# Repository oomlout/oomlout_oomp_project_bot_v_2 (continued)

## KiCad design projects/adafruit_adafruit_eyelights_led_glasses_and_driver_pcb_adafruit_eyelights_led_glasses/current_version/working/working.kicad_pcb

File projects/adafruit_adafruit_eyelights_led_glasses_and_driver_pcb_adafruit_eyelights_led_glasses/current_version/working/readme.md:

# adafruit_eyelights_led_glasses_and_driver_pcb
 
## summary 
* id: adafruit_adafruit_eyelights_led_glasses_and_driver_pcb_adafruit_eyelights_led_glasses
* user: adafruit
* name: adafruit_eyelights_led_glasses_and_driver_pcb
* board: adafruit_eyelights_led_glasses
* repo: https://github.com/adafruit/Adafruit-EyeLights-LED-Glasses-and-Driver-PCB

* src_file_repo_sch: 
* src_file_repo_sch_link: https://github.com/adafruit/Adafruit-EyeLights-LED-Glasses-and-Driver-PCB/tree/main/
* full details link: https://github.com/oomlout/oomlout_oomp_project_bot_v_2/tree/main/projects/adafruit_adafruit_eyelights_led_glasses_and_driver_pcb_adafruit_eyelights_led_glasses/current_version/working  

## schematic  
  
[schematic (pdf)](working_schematic.pdf) 

## pcb  

[board (pdf)](working.pdf)  

## working_bom
| Id | Designator | Footprint | Quantity | Designation | Supplier and ref |  | None | 
| --- | --- | --- | --- | --- | --- | --- | --- | 
| 1 | C10,C3,C4 | 0603-NO | 3 | 0.1uF |  |  | [''] | 
| 2 | R10,R11 | 0603-NO | 2 | 22 |  |  | [''] | 
| 3 | C7,C9,C6,C8,C5,C1 | 0805-NO | 6 | 10uF |  |  | [''] | 
| 4 | IC1 | SPK0415HM4H | 1 | MIC_PDM_SPK0415 |  |  | [''] | 
| 5 | SW1 | SPST_TACTILE_RA | 1 | TACT_RA |  |  | [''] | 
| 6 | FID2,FID1 | FIDUCIAL_1MM | 2 | FIDUCIAL_1MM |  |  | [''] | 
| 7 | D3 | CHIPLED_0805_NOOUTLINE | 1 | ORANGE |  |  | [''] | 
| 8 | U$16,U$14,U$10,U$12 | SLOT_4MM_PLATED | 4 | MOUNTINGHOLE_SLOT4MM |  |  | [''] | 
| 9 | SW2 | EG1390 | 1 | EG11 |  |  | [''] | 
| 10 | IC2 | SOIC8_150MIL | 1 | GD25Q16 |  |  | [''] | 
| 11 | R7,R1,R8,R6 | 0603-NO | 4 | 100K |  |  | [''] | 
| 12 | SW3 | BTN_KMR2_4.6X2.8 | 1 | KMR2 |  |  | [''] | 
| 13 | R2,R3 | 0603-NO | 2 | 1K |  |  | [''] | 
| 14 | X2 | USB_C_CUSB31-CFM2AX-01-X | 1 | USBC |  |  | [''] | 
| 15 | U3 | SOT23-5 | 1 | MCP73831T-2ACI/OT |  |  | [''] | 
| 16 | LED1 | SK6805_1515 | 1 | WS2812B_SK6805_1515 |  |  | [''] | 
| 17 | R12,R9,R4 | 0603-NO | 3 | 5.1K |  |  | [''] | 
| 18 | D2 | CHIPLED_0805_NOOUTLINE | 1 | RED |  |  | [''] | 
| 19 | JP1 | 1X03_ROUND | 1 |  |  |  | [''] | 
| 20 | CONN1 | JST_SH4 | 1 | STEMMA_I2C_QT |  |  | [''] | 
| 21 | IC4 | LGA16_3X3MM | 1 | LIS3DH |  |  | [''] | 
| 22 | Q3 | SOT23-R | 1 | DMG2305 |  |  | [''] | 
| 23 | Q2 | SOT363 | 1 | BSS138 |  |  | [''] | 
| 24 | R5 | RESPACK_4X0603 | 1 | 10K |  |  | [''] | 
| 25 | U2 | SOT23-5 | 1 | AP2112(3.3V) |  |  | [''] | 
| 26 | MDBT1 | MDBT50 | 1 | MDBT50 |  |  | [''] | 
| 27 | X3 | JSTPH2_BATT | 1 | JSTPH |  |  | [''] | 
| 28 | D1 | SOD-123 | 1 | MBR120 |  |  | [''] | 
| 29 | SJ1 | SOLDERJUMPER_ARROW_NOPASTE | 1 |  |  |  | [''] | 
| 30 | U$63 | PCBFEAT-REV-040 | 1 |  |  |  | [''] | 
| 31 | U$37 | ADAFRUIT_TEXT_20MM | 1 |  |  |  | [''] | 
| 32 | U$28 | STEMMAQT | 1 |  |  |  | [''] | 

## bom_schematic
| Ref | Qnty | Value | Cmp name | Footprint | Description | Vendor | DNP | 
| --- | --- | --- | --- | --- | --- | --- | --- | 
| C1, C5, C6, C7, C8, C9 | 6 | 10uF | CAP_CERAMIC0805-NOOUTLINE | working:0805-NO |  |  |  | 
| C3, C4, C10 | 3 | 0.1uF | CAP_CERAMIC0603_NO | working:0603-NO |  |  |  | 
| CONN1 | 1 | STEMMA_I2C_QT | STEMMA_I2C_QT | working:JST_SH4 |  |  |  | 
| D1 | 1 | MBR120 | DIODE-SCHOTTKYSOD-123 | working:SOD-123 |  |  |  | 
| D2 | 1 | RED | LED0805_NOOUTLINE | working:CHIPLED_0805_NOOUTLINE |  |  |  | 
| D3 | 1 | ORANGE | LED0805_NOOUTLINE | working:CHIPLED_0805_NOOUTLINE |  |  |  | 
| FID1, FID2 | 2 | FIDUCIAL_1MM | FIDUCIAL_1MM | working:FIDUCIAL_1MM |  |  |  | 
| IC1 | 1 | MIC_PDM_SPK0415 | MIC_PDM_SPK0415 | working:SPK0415HM4H |  |  |  | 
| IC2 | 1 | GD25Q16 | SPIFLASH_8PIN | working:SOIC8_150MIL |  |  |  | 
| IC4 | 1 | LIS3DH | ACCEL_LIS3DHTR | working:LGA16_3X3MM |  |  |  | 
| JP1 | 1 | HEADER-1X3ROUND | HEADER-1X3ROUND | working:1X03_ROUND |  |  |  | 
| LED1 | 1 | WS2812B_SK6805_1515 | WS2812B_SK6805_1515 | working:SK6805_1515 |  |  |  | 
| MDBT1 | 1 | MDBT50 | MDBT50 | working:MDBT50 |  |  |  | 
| Q2 | 1 | BSS138 | MOSFET-N_DUAL | working:SOT363 |  |  |  | 
| Q3 | 1 | DMG2305 | MOSFET-P | working:SOT23-R |  |  |  | 
| R1, R6, R7, R8 | 4 | 100K | RESISTOR_0603_NOOUT | working:0603-NO |  |  |  | 
| R2, R3 | 2 | 1K | RESISTOR_0603_NOOUT | working:0603-NO |  |  |  | 
| R4, R9, R12 | 3 | 5.1K | RESISTOR_0603_NOOUT | working:0603-NO |  |  |  | 
| R5 | 1 | 10K | RESISTOR_4PACK | working:RESPACK_4X0603 |  |  |  | 
| R10, R11 | 2 | 22 | RESISTOR_0603_NOOUT | working:0603-NO |  |  |  | 
| SJ1 | 1 | SOLDERJUMPER | SOLDERJUMPER | working:SOLDERJUMPER_ARROW_NOPASTE |  |  |  | 
| SW1 | 1 | TACT_RA | SWITCH_SPST_TACT_RA | working:SPST_TACTILE_RA |  |  |  | 
| SW2 | 1 | EG11 | SWITCH_DPDTEG1390 | working:EG1390 |  |  |  | 
| SW3 | 1 | KMR2 | SWITCH_TACT_SMT4.6X2.8 | working:BTN_KMR2_4.6X2.8 |  |  |  | 
| U2 | 1 | AP2112(3.3V) | VREG_SOT23-5 | working:SOT23-5 |  |  |  | 
| U3 | 1 | MCP73831T-2ACI/OT | MCP73831/2 | working:SOT23-5 |  |  |  | 
| U$10, U$12, U$14, U$16 | 4 | MOUNTINGHOLE_SLOT4MM | MOUNTINGHOLE_SLOT4MM | working:SLOT_4MM_PLATED |  |  |  | 
| X2 | 1 | USBC | USB_C | working:USB_C_CUSB31-CFM2AX-01-X |  |  |  | 
| X3 | 1 | JSTPH | CON_JST_PH_2PIN_BATT | working:JSTPH2_BATT |  |  |  |

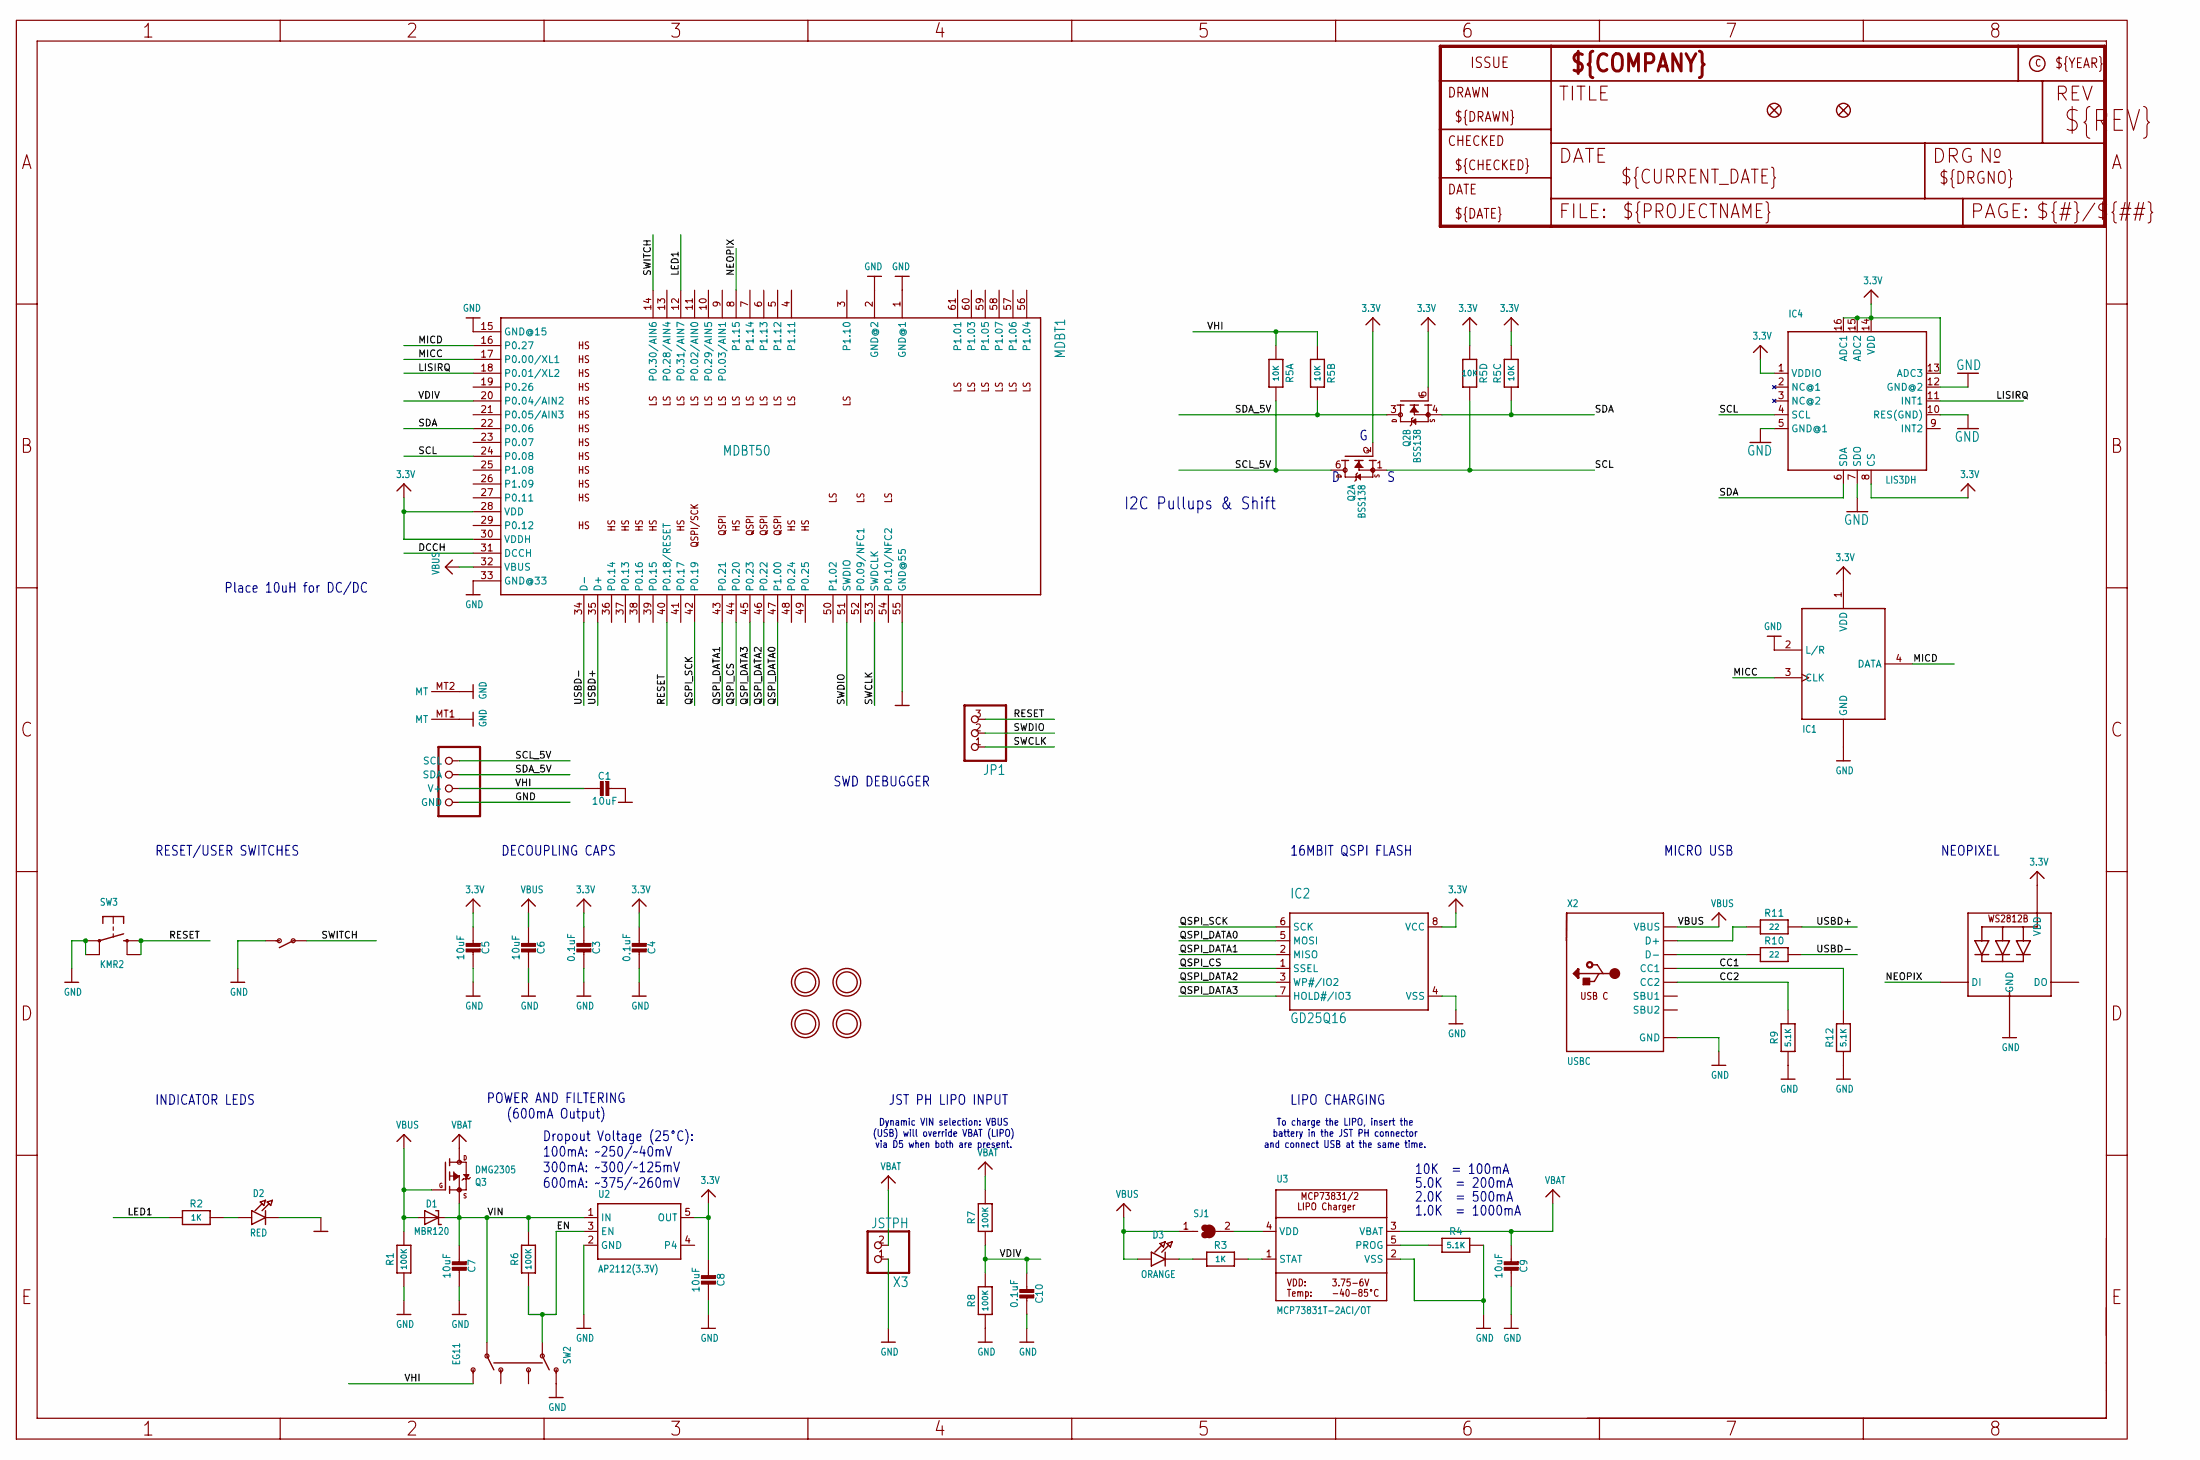
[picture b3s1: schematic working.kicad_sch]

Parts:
C1, C5, C6, C7, C8, C9: 10uF; 0805-NO
C3, C4, C10: 0.1uF; 0603-NO
CONN1: STEMMA_I2C_QT; JST_SH4
D1: MBR120; SOD-123
D2: RED; CHIPLED_0805_NOOUTLINE
D3: ORANGE; CHIPLED_0805_NOOUTLINE
FID1, FID2: FIDUCIAL_1MM
IC1: MIC_PDM_SPK0415; SPK0415HM4H
IC2: GD25Q16; SOIC8_150MIL
IC4: LIS3DH; LGA16_3X3MM
JP1: HEADER-1X3ROUND; 1X03_ROUND
LED1: WS2812B_SK6805_1515; SK6805_1515
MDBT1: MDBT50
Q2: BSS138; SOT363
Q3: DMG2305; SOT23-R
R1, R6, R7, R8: 100K; 0603-NO
R2, R3: 1K; 0603-NO
R4, R9, R12: 5.1K; 0603-NO
R5: 10K; RESPACK_4X0603
R10, R11: 22; 0603-NO
SJ1: SOLDERJUMPER; SOLDERJUMPER_ARROW_NOPASTE
SW1: TACT_RA; SPST_TACTILE_RA
SW2: EG11; EG1390
SW3: KMR2; BTN_KMR2_4.6X2.8
U2: AP2112(3.3V); SOT23-5
U3: MCP73831T-2ACI/OT; SOT23-5
U$10, U$12, U$14, U$16: MOUNTINGHOLE_SLOT4MM; SLOT_4MM_PLATED
X2: USBC; USB_C_CUSB31-CFM2AX-01-X
X3: JSTPH; JSTPH2_BATT

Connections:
3.3V: C3.2, C4.2, C5.2, C8.2, IC1.1 (VDD), IC2.8 (VCC), IC4.1 (VDDIO), IC4.8 (CS), IC4.13 (ADC3), IC4.14 (VDD), IC4.15 (ADC2), IC4.16 (ADC1), LED1.2 (VDD), MDBT1.28 (VDD), MDBT1.30 (VDDH), Q2.2 (G), Q2.5 (G), R5.3 (1), R5.5 (2), U2.5 (OUT)
CC1: R12.2, X2.A5 (CC1)
CC2: R9.2, X2.B5 (CC2)
D+: R11.1, X2.A6 (D+), X2.B6 (D+)
D-: R10.1, X2.A7 (D-), X2.B7 (D-)
DCCH: MDBT1.31 (DCCH)
EN: R6.1, SW2.P1, U2.3 (EN)
GND: C1.1, C3.1, C4.1, C5.1, C6.1, C7.1, C8.1, C9.1, C10.1, CONN1.1 (GND), CONN1.MT1 (MT), CONN1.MT2 (MT), D2.C, IC1.2 (L/R), IC1.5 (GND), IC1.6 (GND), IC1.7 (GND), IC1.8 (GND), IC2.4 (VSS), IC4.5 (GND@1), IC4.7 (SDO), IC4.10 (RES(GND)), IC4.12 (GND@2), LED1.4 (GND), MDBT1.1 (GND@1), MDBT1.2 (GND@2), MDBT1.15 (GND@15), MDBT1.33 (GND@33), MDBT1.55 (GND@55), R1.1, R4.2, R8.1, R9.1, R12.1, SW1.2 (S), SW2.O1, SW3.A, SW3.A' (P1), U2.2 (GND), U3.2 (VSS), X2.A1B12 (GND), X2.B1A12 (GND), X3.1
LED1: MDBT1.12 (P0.31/AIN7), R2.1
LISIRQ: IC4.11 (INT1), MDBT1.18 (P0.01/XL2)
MICC: IC1.3 (CLK), MDBT1.17 (P0.00/XL1)
MICD: IC1.4 (DATA), MDBT1.16 (P0.27)
unnamed: D3.C, R3.1
unnamed: SJ1.2, U3.4 (VDD)
unnamed: D2.A, R2.2
unnamed: R3.2, U3.1 (STAT)
unnamed: R4.1, U3.5 (PROG)
NEOPIX: LED1.1 (DI), MDBT1.8 (P1.15)
QSPI_CS: IC2.1 (SSEL), MDBT1.44 (P0.20)
QSPI_DATA0: IC2.5 (MOSI), MDBT1.47 (P1.00)
QSPI_DATA1: IC2.2 (MISO), MDBT1.43 (P0.21)
QSPI_DATA2: IC2.3 (WP#/IO2), MDBT1.46 (P0.22)
QSPI_DATA3: IC2.7 (HOLD#/IO3), MDBT1.45 (P0.23)
QSPI_SCK: IC2.6 (SCK), MDBT1.42 (P0.19)
RESET: JP1.3, MDBT1.40 (P0.18/RESET), SW3.B (S), SW3.B' (S1)
SCL: IC4.4 (SCL), MDBT1.24 (P0.08), Q2.1 (S), R5.4 (1)
SCL_5V: CONN1.4 (SCL), Q2.6 (D), R5.8 (2)
SDA: IC4.6 (SDA), MDBT1.22 (P0.06), Q2.4 (S), R5.6 (2)
SDA_5V: CONN1.3 (SDA), Q2.3 (D), R5.7 (2)
SWCLK: JP1.1, MDBT1.53 (SWDCLK)
SWDIO: JP1.2, MDBT1.51 (SWDIO)
SWITCH: MDBT1.14 (P0.30/AIN6), SW1.1
USBD+: MDBT1.35 (D+), R11.2
USBD-: MDBT1.34 (D-), R10.2
VBAT: C9.2, Q3.3 (D), R7.2, U3.3 (VBAT), X3.2
VBUS: C6.2, D1.A, D3.A, MDBT1.32 (VBUS), Q3.1 (G), R1.2, SJ1.1, X2.A4B9 (VBUS), X2.B4A9 (VBUS)
VDIV: C10.2, MDBT1.20 (P0.04/AIN2), R7.1, R8.2
VHI: C1.2, CONN1.2 (V+), R5.1, R5.2 (1), SW2.S2
VIN: C7.2, D1.C, Q3.2 (S), R6.2, SW2.P2, U2.1 (IN)

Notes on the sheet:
POWER AND FILTERING (600mA Output)
5.0K = 200mA
MICRO USB
SWD DEBUGGER
Dynamic VIN selection: VBUS (USB) will override VBAT (LIPO) via D5 when both are present.
16MBIT QSPI FLASH
JST PH LIPO INPUT
Dropout Voltage (25°C): 100mA: ~250/~40mV 300mA: ~300/~125mV 600mA: ~375/~260mV
NEOPIXEL
1.0K = 1000mA
INDICATOR LEDS
DECOUPLING CAPS
2.0K = 500mA
Place 10uH for DC/DC
10K = 100mA
LIPO CHARGING
To charge the LIPO, insert the battery in the JST PH connector and connect USB at the same time.
I2C Pullups & Shift
RESET/USER SWITCHES

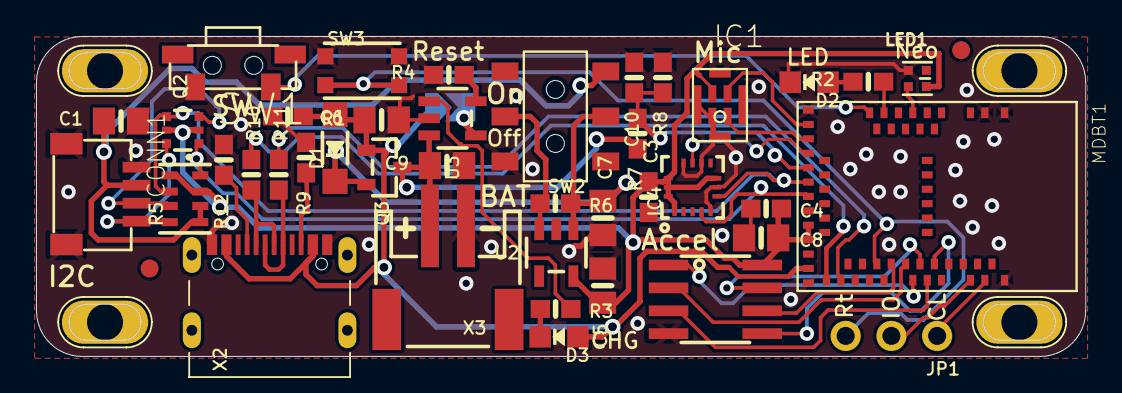
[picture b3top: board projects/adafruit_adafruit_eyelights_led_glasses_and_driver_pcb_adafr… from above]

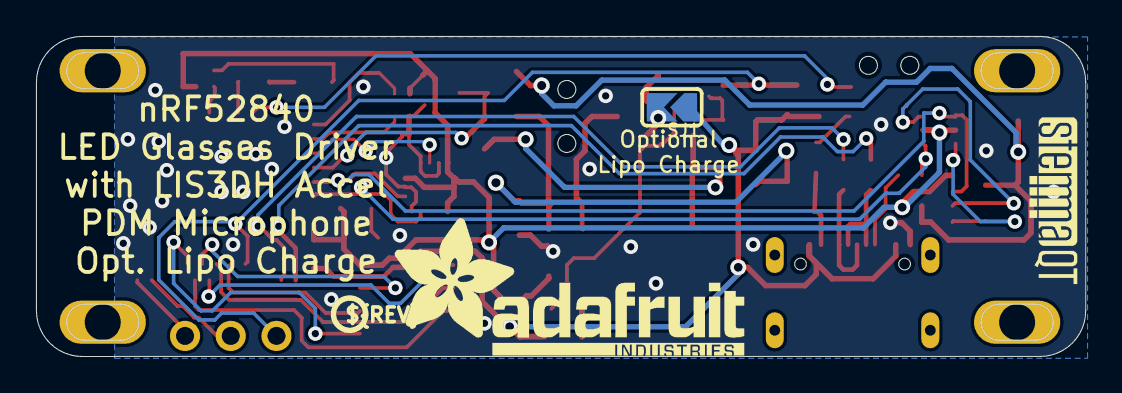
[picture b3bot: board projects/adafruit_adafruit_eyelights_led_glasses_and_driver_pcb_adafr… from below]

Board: 2 copper layers, 58.3 x 17.8 mm, 50 parts (4 on the bottom side), 38 nets.

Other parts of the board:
U$28: STEMMAQT
U$37: ADAFRUIT_TEXT_20MM
U$63: PCBFEAT-REV-040

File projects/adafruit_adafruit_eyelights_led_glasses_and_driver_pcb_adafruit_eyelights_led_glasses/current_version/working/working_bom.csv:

"Id";"Designator";"Footprint";"Quantity";"Designation";"Supplier and ref";
1;"C10,C3,C4";"0603-NO";3;"0.1uF";;;
2;"R10,R11";"0603-NO";2;"22";;;
3;"C7,C9,C6,C8,C5,C1";"0805-NO";6;"10uF";;;
4;"IC1";"SPK0415HM4H";1;"MIC_PDM_SPK0415";;;
5;"SW1";"SPST_TACTILE_RA";1;"TACT_RA";;;
6;"FID2,FID1";"FIDUCIAL_1MM";2;"FIDUCIAL_1MM";;;
7;"D3";"CHIPLED_0805_NOOUTLINE";1;"ORANGE";;;
8;"U$16,U$14,U$10,U$12";"SLOT_4MM_PLATED";4;"MOUNTINGHOLE_SLOT4MM";;;
9;"SW2";"EG1390";1;"EG11";;;
10;"IC2";"SOIC8_150MIL";1;"GD25Q16";;;
11;"R7,R1,R8,R6";"0603-NO";4;"100K";;;
12;"SW3";"BTN_KMR2_4.6X2.8";1;"KMR2";;;
13;"R2,R3";"0603-NO";2;"1K";;;
14;"X2";"USB_C_CUSB31-CFM2AX-01-X";1;"USBC";;;
15;"U3";"SOT23-5";1;"MCP73831T-2ACI/OT";;;
16;"LED1";"SK6805_1515";1;"WS2812B_SK6805_1515";;;
17;"R12,R9,R4";"0603-NO";3;"5.1K";;;
18;"D2";"CHIPLED_0805_NOOUTLINE";1;"RED";;;
19;"JP1";"1X03_ROUND";1;"";;;
20;"CONN1";"JST_SH4";1;"STEMMA_I2C_QT";;;
21;"IC4";"LGA16_3X3MM";1;"LIS3DH";;;
22;"Q3";"SOT23-R";1;"DMG2305";;;
23;"Q2";"SOT363";1;"BSS138";;;
24;"R5";"RESPACK_4X0603";1;"10K";;;
25;"U2";"SOT23-5";1;"AP2112(3.3V)";;;
26;"MDBT1";"MDBT50";1;"MDBT50";;;
27;"X3";"JSTPH2_BATT";1;"JSTPH";;;
28;"D1";"SOD-123";1;"MBR120";;;
29;"SJ1";"SOLDERJUMPER_ARROW_NOPASTE";1;"";;;
30;"U$63";"PCBFEAT-REV-040";1;"";;;
31;"U$37";"ADAFRUIT_TEXT_20MM";1;"";;;
32;"U$28";"STEMMAQT";1;"";;;

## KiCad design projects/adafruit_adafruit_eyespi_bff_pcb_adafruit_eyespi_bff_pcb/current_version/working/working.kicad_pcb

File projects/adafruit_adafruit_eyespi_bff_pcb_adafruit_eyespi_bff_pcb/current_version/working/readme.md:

# adafruit_eyespi_bff_pcb
 
## summary 
* id: adafruit_adafruit_eyespi_bff_pcb_adafruit_eyespi_bff_pcb
* user: adafruit
* name: adafruit_eyespi_bff_pcb
* board: adafruit_eyespi_bff_pcb
* repo: https://github.com/adafruit/Adafruit-EYESPI-BFF-PCB

* src_file_repo_sch: 
* src_file_repo_sch_link: https://github.com/adafruit/Adafruit-EYESPI-BFF-PCB/tree/main/
* full details link: https://github.com/oomlout/oomlout_oomp_project_bot_v_2/tree/main/projects/adafruit_adafruit_eyespi_bff_pcb_adafruit_eyespi_bff_pcb/current_version/working  

## schematic  
  
[schematic (pdf)](working_schematic.pdf) 

## pcb  

[board (pdf)](working.pdf)  

## working_bom
| Id | Designator | Footprint | Quantity | Designation | Supplier and ref |  | None | 
| --- | --- | --- | --- | --- | --- | --- | --- | 
| 1 | SJ5,SJ2,SJ4,SJ3,SJ1,SJ6 | SOLDERJUMPER_CLOSEDWIRE | 6 |  |  |  | [''] | 
| 2 | PLABEL27 | PLABEL27 | 1 |  |  |  | [''] | 
| 3 | PLABEL5 | PLABEL5 | 1 |  |  |  | [''] | 
| 4 | PLABEL2 | PLABEL2 | 1 |  |  |  | [''] | 
| 5 | PLABEL26 | PLABEL26 | 1 |  |  |  | [''] | 
| 6 | PLABEL9 | PLABEL9 | 1 |  |  |  | [''] | 
| 7 | PLABEL8 | PLABEL8 | 1 |  |  |  | [''] | 
| 8 | JP2,JP6,JP8,JP5,JP4,JP7,JP10,JP9 | 1X01_2MM | 8 |  |  |  | [''] | 
| 9 | PLABEL22 | PLABEL22 | 1 |  |  |  | [''] | 
| 10 | PLABEL28 | PLABEL28 | 1 |  |  |  | [''] | 
| 11 | PLABEL1 | PLABEL1 | 1 |  |  |  | [''] | 
| 12 | U$6,U$8 | FIDUCIAL_1MM | 2 | FIDUCIAL_1MM |  |  | [''] | 
| 13 | PLABEL23 | PLABEL23 | 1 |  |  |  | [''] | 
| 14 | PLABEL25 | PLABEL25 | 1 |  |  |  | [''] | 
| 15 | PLABEL11 | PLABEL11 | 1 |  |  |  | [''] | 
| 16 | PLABEL3 | PLABEL3 | 1 |  |  |  | [''] | 
| 17 | PLABEL13 | PLABEL13 | 1 |  |  |  | [''] | 
| 18 | PLABEL14 | PLABEL14 | 1 |  |  |  | [''] | 
| 19 | PLABEL7 | PLABEL7 | 1 |  |  |  | [''] | 
| 20 | PLABEL20 | PLABEL20 | 1 |  |  |  | [''] | 
| 21 | PLABEL21 | PLABEL21 | 1 |  |  |  | [''] | 
| 22 | X1 | EYE_SPI_DISPLAY_SLIM | 1 | EYE_SPI_DISPLAY_SLIM |  |  | [''] | 
| 23 | PLABEL12 | PLABEL12 | 1 |  |  |  | [''] | 
| 24 | PLABEL10 | PLABEL10 | 1 |  |  |  | [''] | 
| 25 | PLABEL24 | PLABEL24 | 1 |  |  |  | [''] | 
| 26 | PLABEL4 | PLABEL4 | 1 |  |  |  | [''] | 
| 27 | PLABEL6 | PLABEL6 | 1 |  |  |  | [''] | 
| 28 | JP3,JP1 | 1X07_CASTEL | 2 |  |  |  | [''] | 
| 29 | U$3 | PCBFEAT-REV-040 | 1 |  |  |  | [''] | 
| 30 | PLABEL31 | PLABEL31 | 1 |  |  |  | [''] | 
| 31 | PLABEL29 | PLABEL29 | 1 |  |  |  | [''] | 
| 32 | PLABEL32 | PLABEL32 | 1 |  |  |  | [''] | 
| 33 | PLABEL19 | PLABEL19 | 1 |  |  |  | [''] | 
| 34 | PLABEL35 | PLABEL35 | 1 |  |  |  | [''] | 
| 35 | PLABEL30 | PLABEL30 | 1 |  |  |  | [''] | 
| 36 | PLABEL34 | PLABEL34 | 1 |  |  |  | [''] | 
| 37 | PLABEL36 | PLABEL36 | 1 |  |  |  | [''] | 
| 38 | PLABEL33 | PLABEL33 | 1 |  |  |  | [''] | 
| 39 | PLABEL37 | PLABEL37 | 1 |  |  |  | [''] | 
| 40 | U$2 | ADAFRUIT_3.5MM | 1 |  |  |  | [''] | 

## bom_schematic
| Ref | Qnty | Value | Cmp name | Footprint | Description | Vendor | DNP | 
| --- | --- | --- | --- | --- | --- | --- | --- | 
| JP1, JP3 | 2 | HEADER-1X7_CASTEL | HEADER-1X7_CASTEL | working:1X07_CASTEL |  |  |  | 
| JP2, JP4, JP5, JP6, JP7, JP8, JP9, JP10 | 8 | HEADER-1X12MM | HEADER-1X12MM | working:1X01_2MM |  |  |  | 
| SJ1, SJ2, SJ3, SJ4, SJ5, SJ6 | 6 | SOLDERJUMPER_CLOSED | SOLDERJUMPER_CLOSED | working:SOLDERJUMPER_CLOSEDWIRE |  |  |  | 
| U$6, U$8 | 2 | FIDUCIAL_1MM | FIDUCIAL_1MM | working:FIDUCIAL_1MM |  |  |  | 
| X1 | 1 | EYE_SPI_DISPLAY_SLIM | EYE_SPI_DISPLAY_SLIM | working:EYE_SPI_DISPLAY_SLIM |  |  |  |

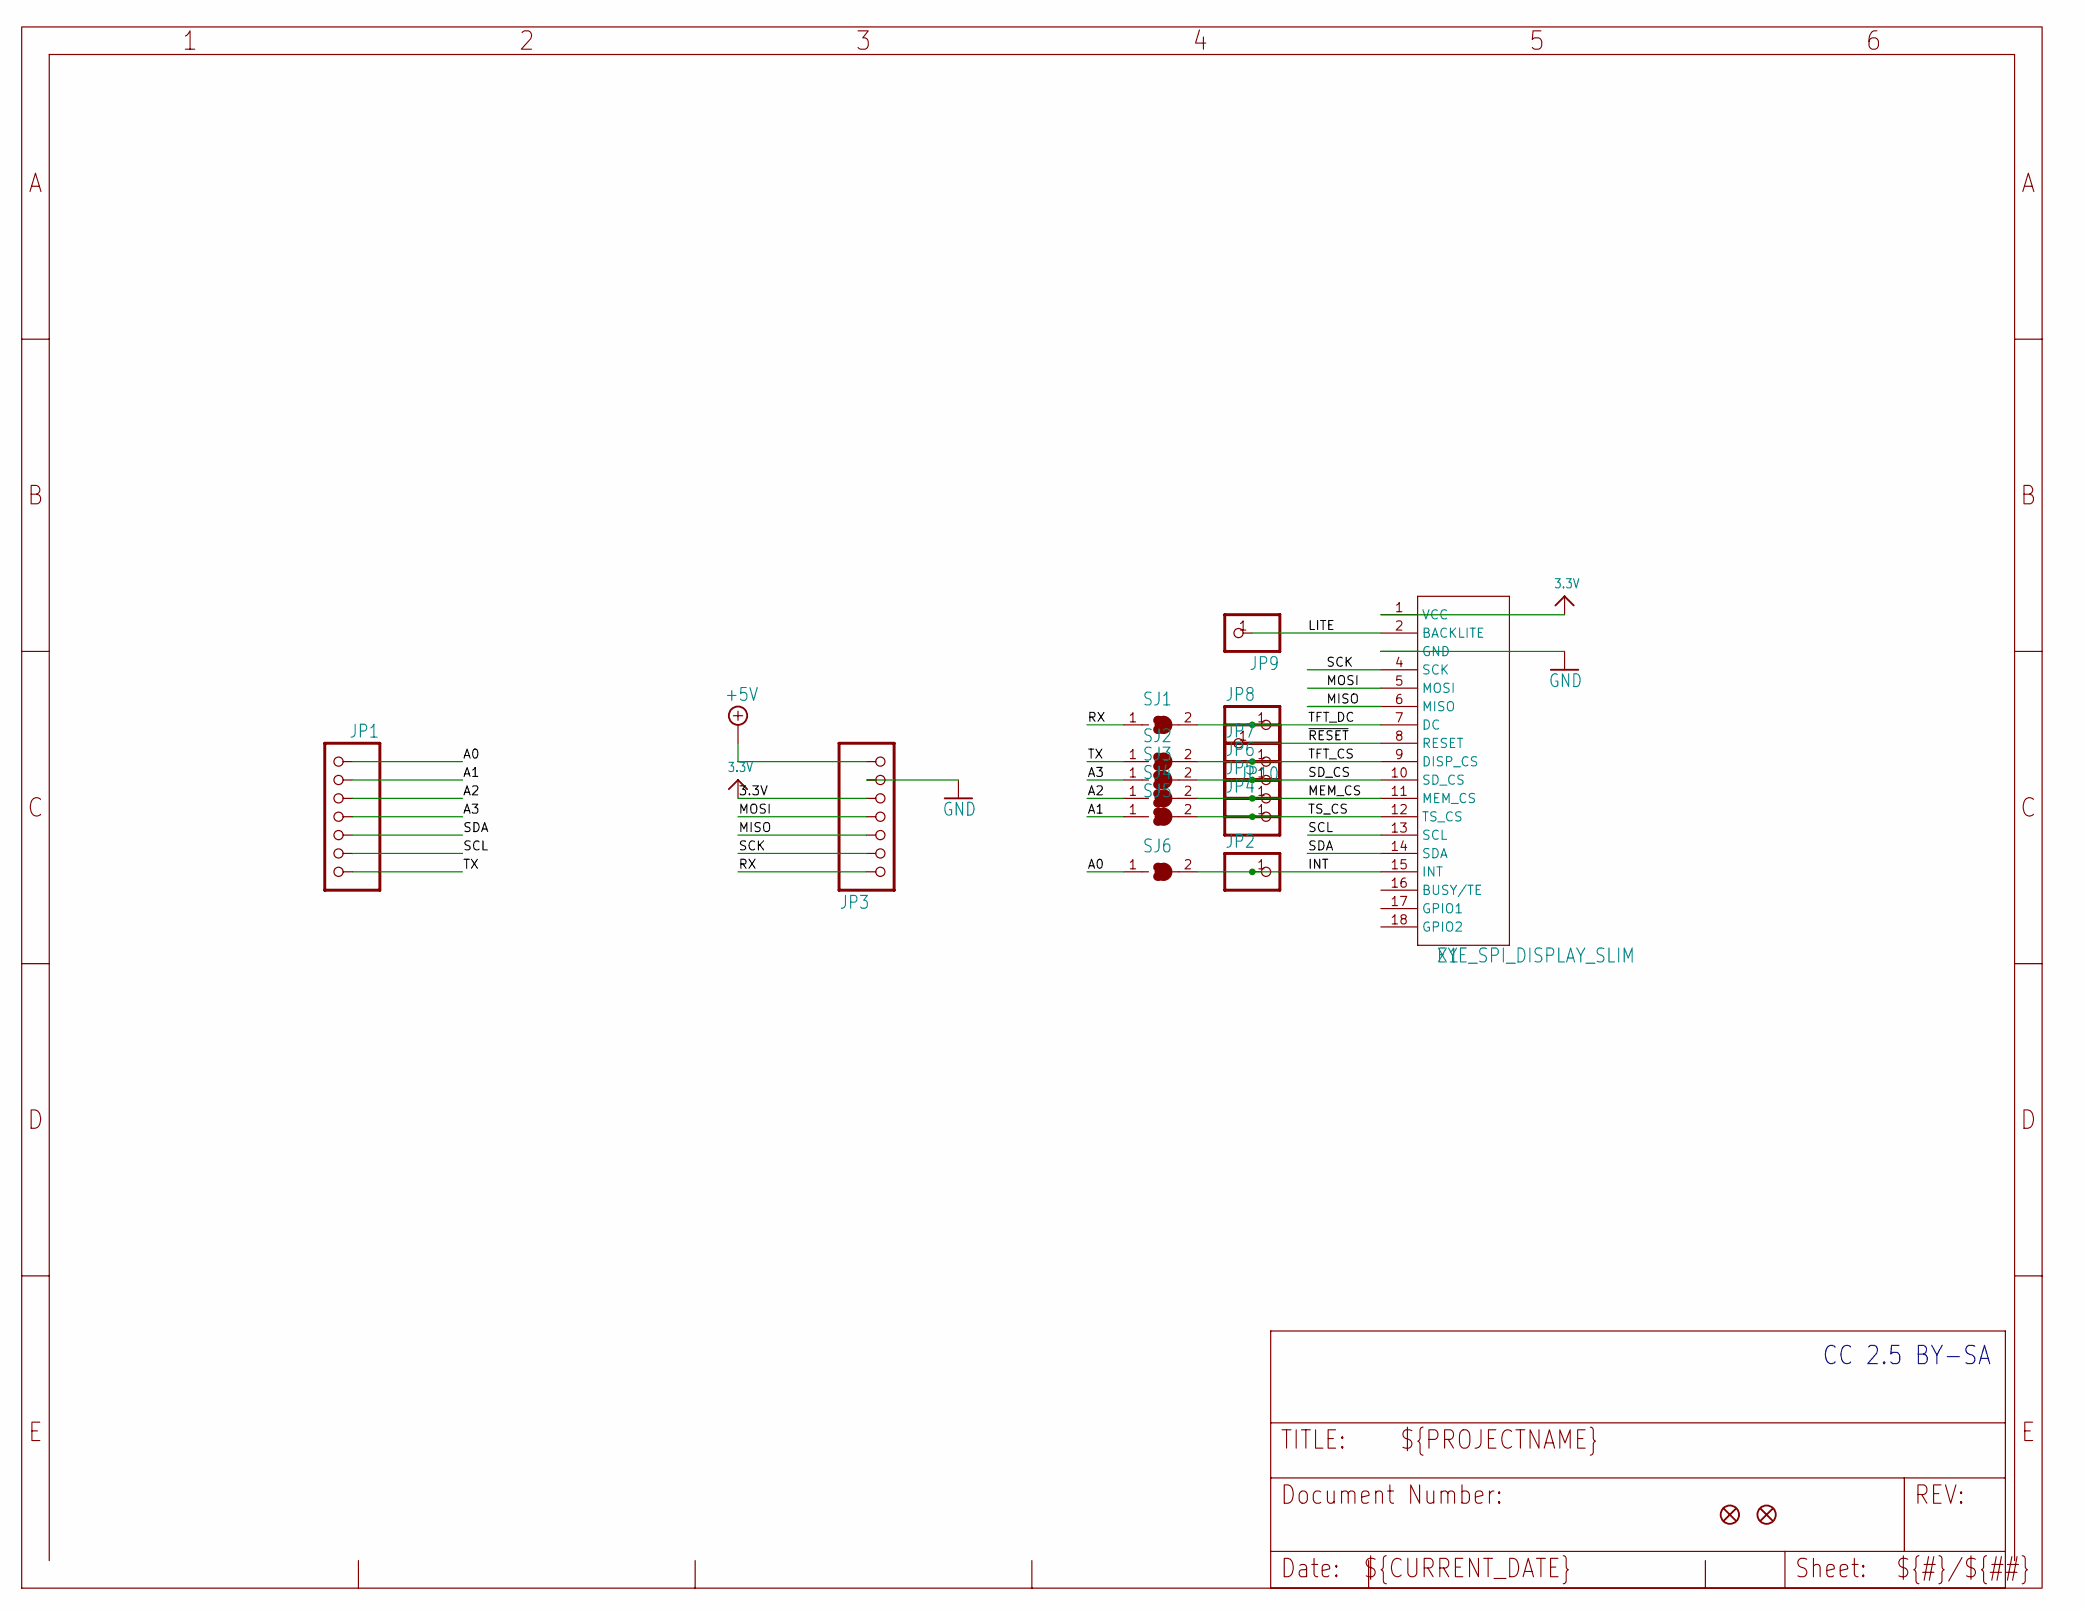
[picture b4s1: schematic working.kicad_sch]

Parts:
JP1, JP3: HEADER-1X7_CASTEL; 1X07_CASTEL
JP2, JP4, JP5, JP6, JP7, JP8, JP9, JP10: HEADER-1X12MM; 1X01_2MM
SJ1, SJ2, SJ3, SJ4, SJ5, SJ6: SOLDERJUMPER_CLOSED; SOLDERJUMPER_CLOSEDWIRE
U$6, U$8: FIDUCIAL_1MM
X1: EYE_SPI_DISPLAY_SLIM

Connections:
3.3V: JP3.5, JP3.5C (5), X1.1 (VCC)
+5V: JP3.7, JP3.7C (7)
A0: JP1.1, JP1.1C (1), SJ6.1
A1: JP1.2, JP1.2C (2), SJ5.1
A2: JP1.3, JP1.3C (3), SJ4.1
A3: JP1.4, JP1.4C (4), SJ3.1
GND: JP3.6, JP3.6C (6), X1.3 (GND), X1.SUPPORT1 (GND), X1.SUPPORT2 (GND)
INT: JP2.1, SJ6.2, X1.15 (INT)
LITE: JP9.1, X1.2 (BACKLITE)
MEM_CS: JP5.1, SJ4.2, X1.11 (MEM_CS)
MISO: JP3.3, JP3.3C (3), X1.6 (MISO)
MOSI: JP3.4, JP3.4C (4), X1.5 (MOSI)
RX: JP3.1, JP3.1C (1), SJ1.1
SCK: JP3.2, JP3.2C (2), X1.4 (SCK)
SCL: JP1.6, JP1.6C (6), X1.13 (SCL)
SDA: JP1.5, JP1.5C (5), X1.14 (SDA)
SD_CS: JP6.1, SJ3.2, X1.10 (SD_CS)
TFT_CS: JP7.1, SJ2.2, X1.9 (DISP_CS)
TFT_DC: JP8.1, SJ1.2, X1.7 (DC)
TS_CS: JP4.1, SJ5.2, X1.12 (TS_CS)
TX: JP1.7, JP1.7C (7), SJ2.1
~RESET: JP10.1, X1.8 (RESET)

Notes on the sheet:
CC 2.5 BY-SA

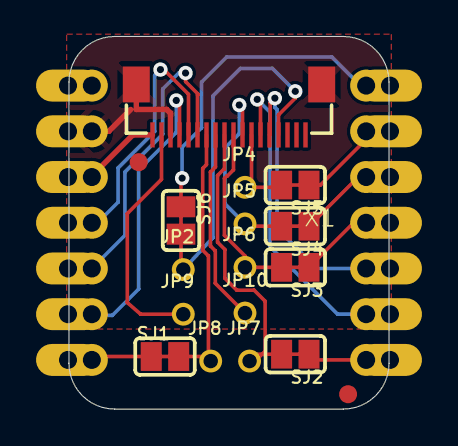
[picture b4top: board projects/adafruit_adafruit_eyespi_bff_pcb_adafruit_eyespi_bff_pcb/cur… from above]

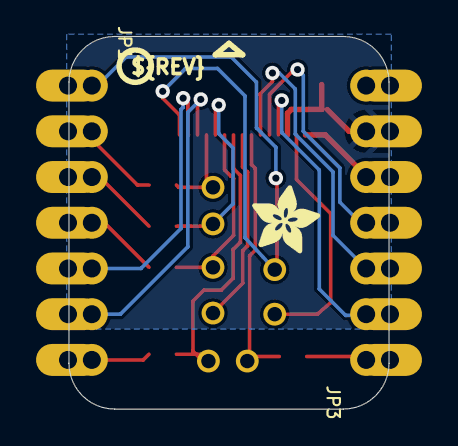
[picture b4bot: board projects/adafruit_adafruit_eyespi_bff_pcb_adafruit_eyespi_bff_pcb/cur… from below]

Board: 16 copper layers, 17.8 x 20.7 mm, 54 parts (14 on the bottom side), 22 nets.

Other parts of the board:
PLABEL1: PLABEL1
PLABEL2: PLABEL2
PLABEL3: PLABEL3
PLABEL4: PLABEL4
PLABEL5: PLABEL5
PLABEL6: PLABEL6
PLABEL7: PLABEL7
PLABEL8: PLABEL8
PLABEL9: PLABEL9
PLABEL10: PLABEL10
PLABEL11: PLABEL11
PLABEL12: PLABEL12
PLABEL13: PLABEL13
PLABEL14: PLABEL14
PLABEL19: PLABEL19
PLABEL20: PLABEL20
PLABEL21: PLABEL21
PLABEL22: PLABEL22
PLABEL23: PLABEL23
PLABEL24: PLABEL24
PLABEL25: PLABEL25
PLABEL26: PLABEL26
PLABEL27: PLABEL27
PLABEL28: PLABEL28
PLABEL29: PLABEL29
PLABEL30: PLABEL30
PLABEL31: PLABEL31
PLABEL32: PLABEL32
PLABEL33: PLABEL33
PLABEL34: PLABEL34
PLABEL35: PLABEL35
PLABEL36: PLABEL36
PLABEL37: PLABEL37
U$2: ADAFRUIT_3.5MM
U$3: PCBFEAT-REV-040

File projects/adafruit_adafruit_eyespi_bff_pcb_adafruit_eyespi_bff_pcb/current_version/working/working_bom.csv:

"Id";"Designator";"Footprint";"Quantity";"Designation";"Supplier and ref";
1;"SJ5,SJ2,SJ4,SJ3,SJ1,SJ6";"SOLDERJUMPER_CLOSEDWIRE";6;"";;;
2;"PLABEL27";"PLABEL27";1;"";;;
3;"PLABEL5";"PLABEL5";1;"";;;
4;"PLABEL2";"PLABEL2";1;"";;;
5;"PLABEL26";"PLABEL26";1;"";;;
6;"PLABEL9";"PLABEL9";1;"";;;
7;"PLABEL8";"PLABEL8";1;"";;;
8;"JP2,JP6,JP8,JP5,JP4,JP7,JP10,JP9";"1X01_2MM";8;"";;;
9;"PLABEL22";"PLABEL22";1;"";;;
10;"PLABEL28";"PLABEL28";1;"";;;
11;"PLABEL1";"PLABEL1";1;"";;;
12;"U$6,U$8";"FIDUCIAL_1MM";2;"FIDUCIAL_1MM";;;
13;"PLABEL23";"PLABEL23";1;"";;;
14;"PLABEL25";"PLABEL25";1;"";;;
15;"PLABEL11";"PLABEL11";1;"";;;
16;"PLABEL3";"PLABEL3";1;"";;;
17;"PLABEL13";"PLABEL13";1;"";;;
18;"PLABEL14";"PLABEL14";1;"";;;
19;"PLABEL7";"PLABEL7";1;"";;;
20;"PLABEL20";"PLABEL20";1;"";;;
21;"PLABEL21";"PLABEL21";1;"";;;
22;"X1";"EYE_SPI_DISPLAY_SLIM";1;"EYE_SPI_DISPLAY_SLIM";;;
23;"PLABEL12";"PLABEL12";1;"";;;
24;"PLABEL10";"PLABEL10";1;"";;;
25;"PLABEL24";"PLABEL24";1;"";;;
26;"PLABEL4";"PLABEL4";1;"";;;
27;"PLABEL6";"PLABEL6";1;"";;;
28;"JP3,JP1";"1X07_CASTEL";2;"";;;
29;"U$3";"PCBFEAT-REV-040";1;"";;;
30;"PLABEL31";"PLABEL31";1;"";;;
31;"PLABEL29";"PLABEL29";1;"";;;
32;"PLABEL32";"PLABEL32";1;"";;;
33;"PLABEL19";"PLABEL19";1;"";;;
34;"PLABEL35";"PLABEL35";1;"";;;
35;"PLABEL30";"PLABEL30";1;"";;;
36;"PLABEL34";"PLABEL34";1;"";;;
37;"PLABEL36";"PLABEL36";1;"";;;
38;"PLABEL33";"PLABEL33";1;"";;;
39;"PLABEL37";"PLABEL37";1;"";;;
40;"U$2";"ADAFRUIT_3.5MM";1;"";;;

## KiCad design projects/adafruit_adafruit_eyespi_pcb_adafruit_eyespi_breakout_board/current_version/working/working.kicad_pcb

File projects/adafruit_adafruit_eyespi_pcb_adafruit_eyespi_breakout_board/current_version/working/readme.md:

# adafruit_eyespi_pcb
 
## summary 
* id: adafruit_adafruit_eyespi_pcb_adafruit_eyespi_breakout_board
* user: adafruit
* name: adafruit_eyespi_pcb
* board: adafruit_eyespi_breakout_board
* repo: https://github.com/adafruit/Adafruit-EYESPI-PCB

* src_file_repo_sch: 
* src_file_repo_sch_link: https://github.com/adafruit/Adafruit-EYESPI-PCB/tree/main/
* full details link: https://github.com/oomlout/oomlout_oomp_project_bot_v_2/tree/main/projects/adafruit_adafruit_eyespi_pcb_adafruit_eyespi_breakout_board/current_version/working  

## schematic  
  
[schematic (pdf)](working_schematic.pdf) 

## pcb  

[board (pdf)](working.pdf)  

## working_bom
| Id | Designator | Footprint | Quantity | Designation | Supplier and ref |  | None | 
| --- | --- | --- | --- | --- | --- | --- | --- | 
| 1 | U$10,U$9 | MOUNTINGHOLE_2.5_PLATED | 2 | MOUNTINGHOLE2.5 |  |  | [''] | 
| 2 | JP2,JP1 | 1X09_ROUND_70 | 2 |  |  |  | [''] | 
| 3 | U$4,U$5 | FIDUCIAL_1MM | 2 | FIDUCIAL_1MM |  |  | [''] | 
| 4 | X1 | EYE_SPI_DISPLAY_BOTCONTACT | 1 | EYE_SPI_DISPLAY_FLIP |  |  | [''] | 
| 5 | U$2 | PCBFEAT-REV-040 | 1 |  |  |  | [''] | 
| 6 | U$22 | EYESPI_MINI_LOGO | 1 |  |  |  | [''] | 

## bom_schematic
| Ref | Qnty | Value | Cmp name | Footprint | Description | Vendor | DNP | 
| --- | --- | --- | --- | --- | --- | --- | --- | 
| JP1, JP2 | 2 | HEADER-1X970MIL | HEADER-1X970MIL | working:1X09_ROUND_70 |  |  |  | 
| U$4, U$5 | 2 | FIDUCIAL_1MM | FIDUCIAL_1MM | working:FIDUCIAL_1MM |  |  |  | 
| U$9, U$10 | 2 | MOUNTINGHOLE2.5 | MOUNTINGHOLE2.5 | working:MOUNTINGHOLE_2.5_PLATED |  |  |  | 
| X1 | 1 | EYE_SPI_DISPLAY_FLIP | EYE_SPI_DISPLAY_FLIP | working:EYE_SPI_DISPLAY_BOTCONTACT |  |  |  | 

## mounting_holes
| x | y | package | value | ref | size | 
| --- | --- | --- | --- | --- | --- | 
| 0.0 | 0.0 | MOUNTINGHOLE_2.5_PLATED | MOUNTINGHOLE2.5 | U$9 | m3 | 
| 20.32 | 0.0 | MOUNTINGHOLE_2.5_PLATED | MOUNTINGHOLE2.5 | U$10 | m3 |

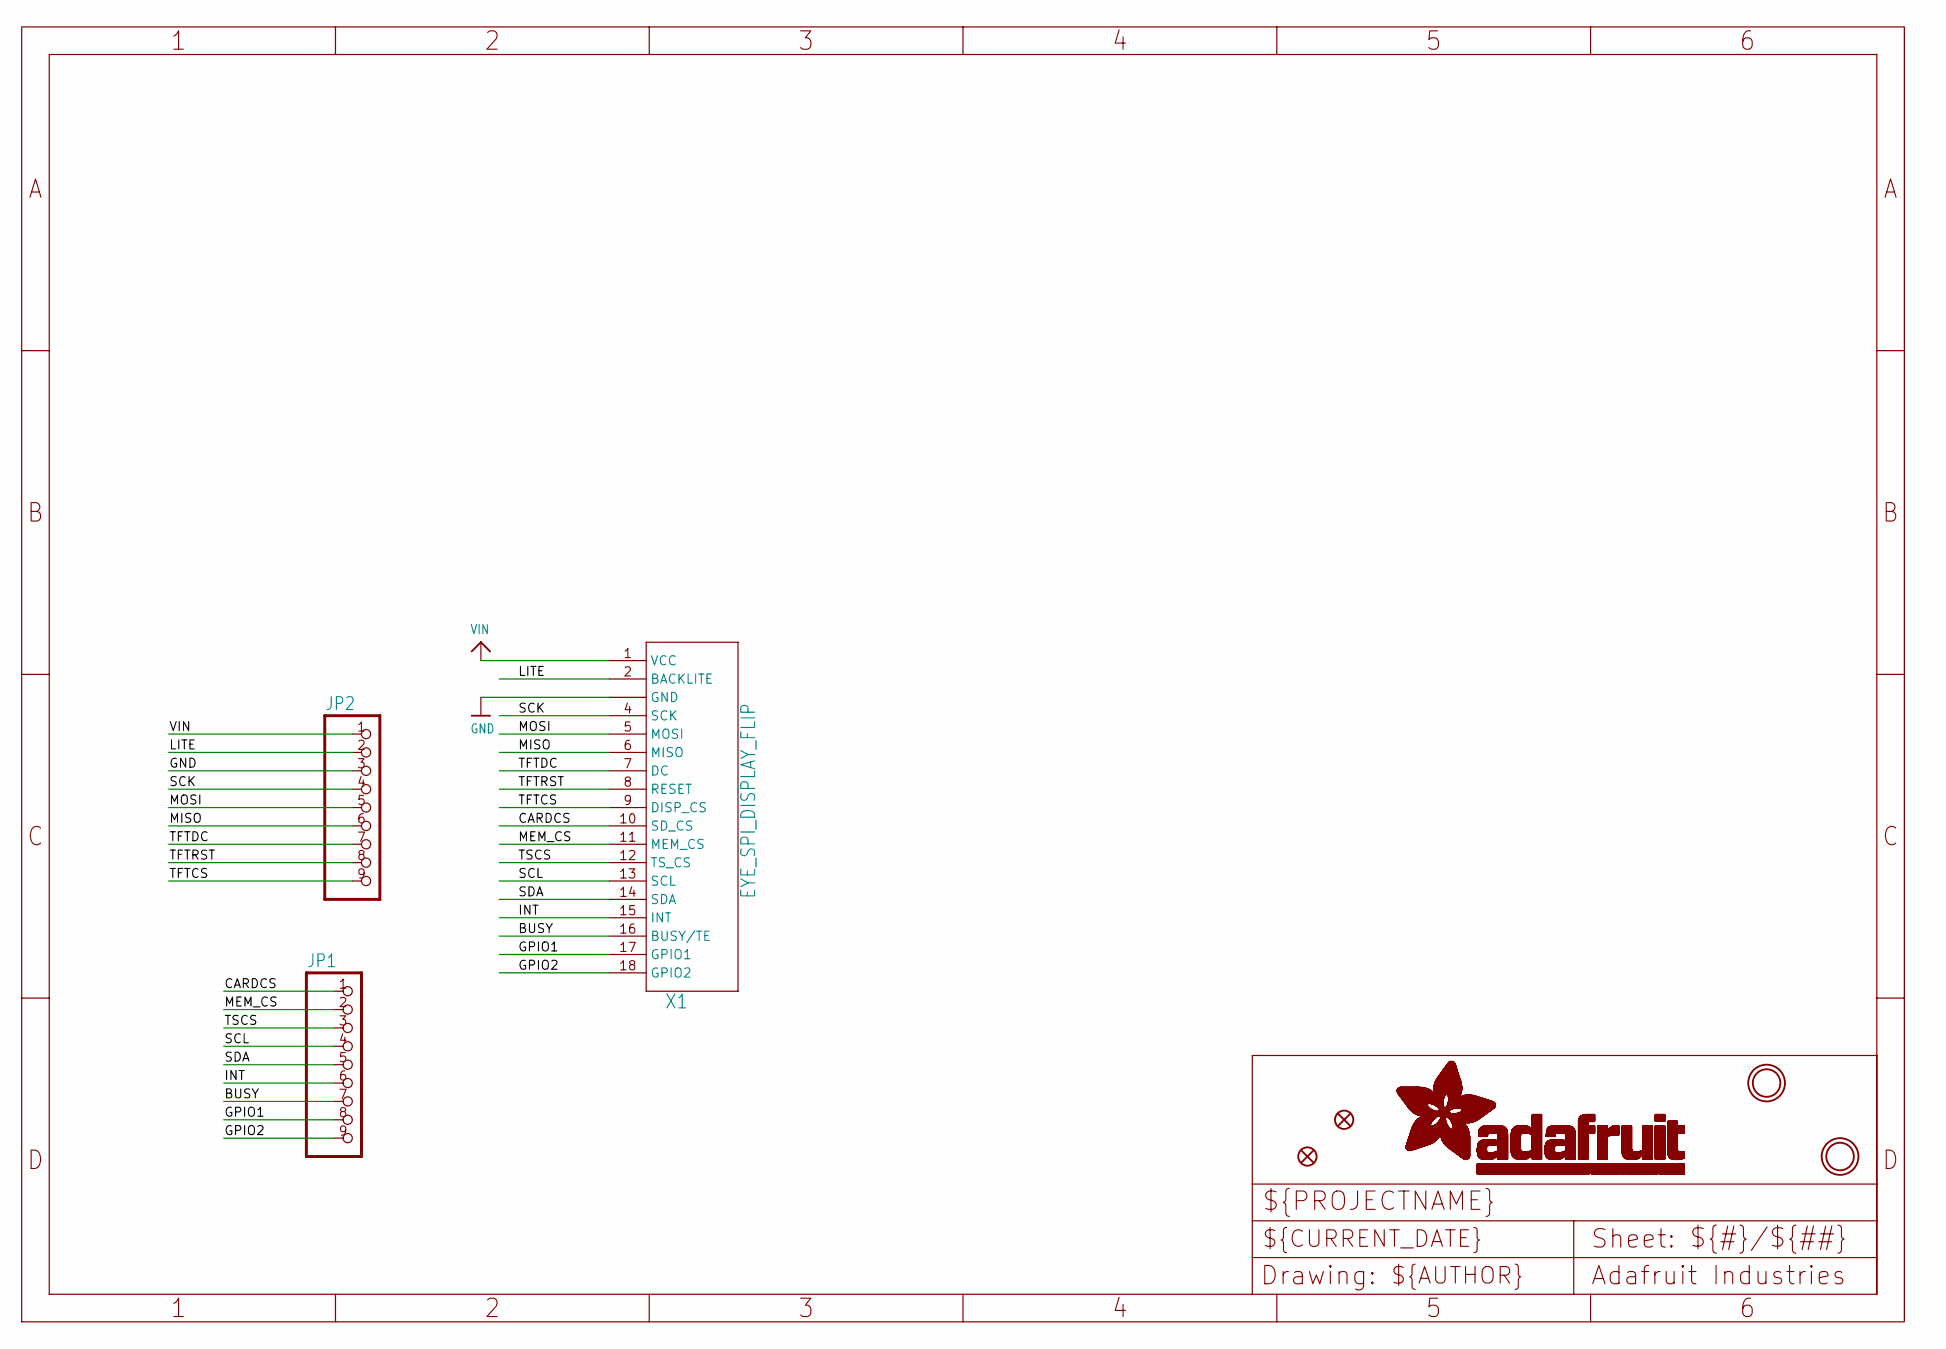
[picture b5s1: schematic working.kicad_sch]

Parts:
JP1, JP2: HEADER-1X970MIL; 1X09_ROUND_70
U$4, U$5: FIDUCIAL_1MM
U$9, U$10: MOUNTINGHOLE2.5; MOUNTINGHOLE_2.5_PLATED
X1: EYE_SPI_DISPLAY_FLIP; EYE_SPI_DISPLAY_BOTCONTACT

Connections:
BUSY: JP1.7, X1.16 (BUSY/TE)
CARDCS: JP1.1, X1.10 (SD_CS)
GND: JP2.3, X1.3 (GND), X1.SUPPORT1 (GND), X1.SUPPORT2 (GND)
GPIO1: JP1.8, X1.17 (GPIO1)
GPIO2: JP1.9, X1.18 (GPIO2)
INT: JP1.6, X1.15 (INT)
LITE: JP2.2, X1.2 (BACKLITE)
MEM_CS: JP1.2, X1.11 (MEM_CS)
MISO: JP2.6, X1.6 (MISO)
MOSI: JP2.5, X1.5 (MOSI)
SCK: JP2.4, X1.4 (SCK)
SCL: JP1.4, X1.13 (SCL)
SDA: JP1.5, X1.14 (SDA)
TFTCS: JP2.9, X1.9 (DISP_CS)
TFTDC: JP2.7, X1.7 (DC)
TFTRST: JP2.8, X1.8 (RESET)
TSCS: JP1.3, X1.12 (TS_CS)
VIN: JP2.1, X1.1 (VCC)

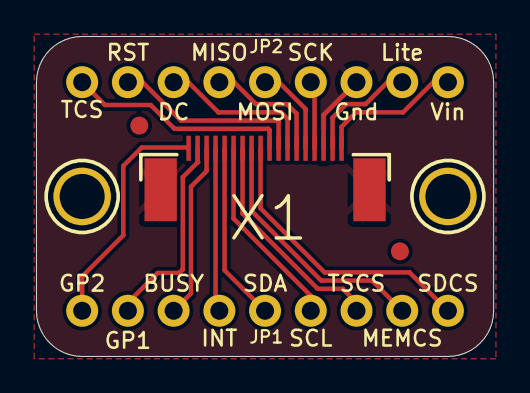
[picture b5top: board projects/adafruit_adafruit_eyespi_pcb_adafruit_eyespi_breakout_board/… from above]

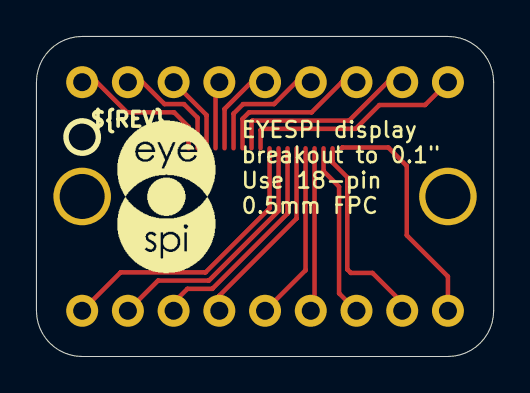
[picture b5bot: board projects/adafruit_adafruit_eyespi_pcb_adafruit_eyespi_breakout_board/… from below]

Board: 16 copper layers, 25.4 x 17.8 mm, 9 parts (2 on the bottom side), 18 nets.

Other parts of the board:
U$2: PCBFEAT-REV-040
U$22: EYESPI_MINI_LOGO
